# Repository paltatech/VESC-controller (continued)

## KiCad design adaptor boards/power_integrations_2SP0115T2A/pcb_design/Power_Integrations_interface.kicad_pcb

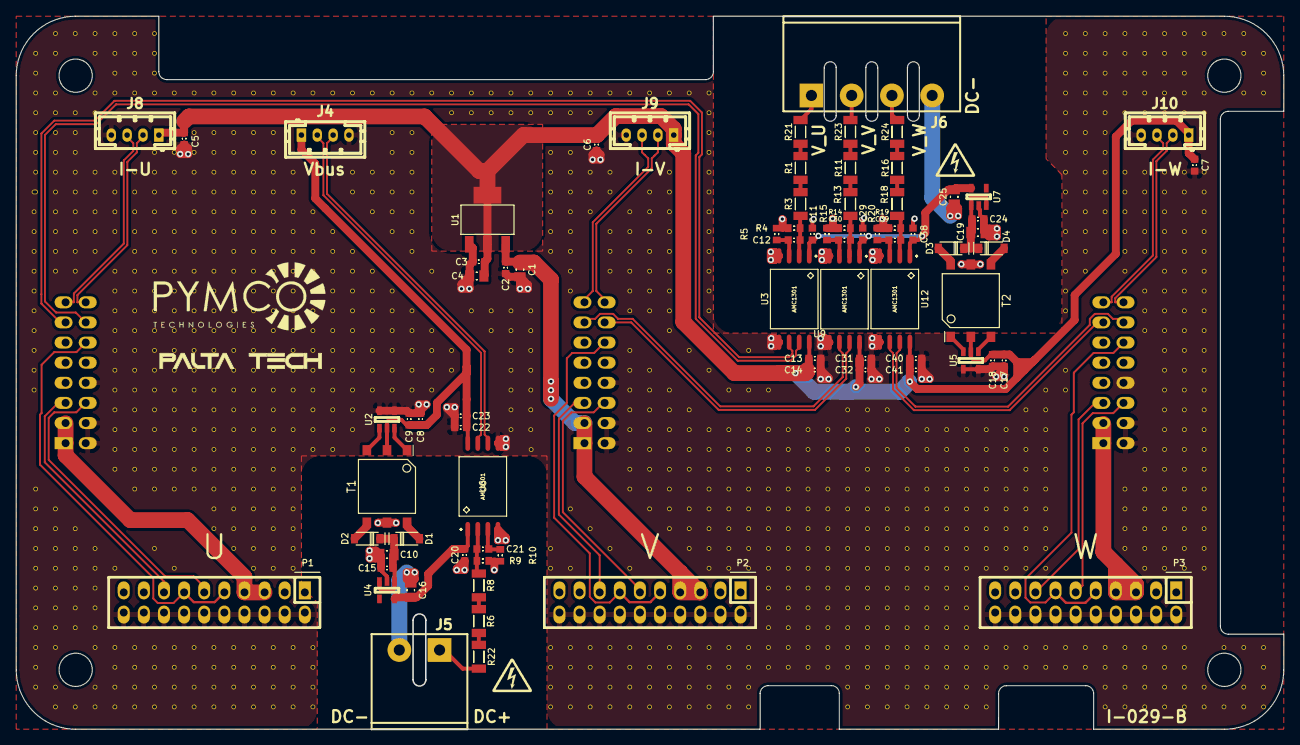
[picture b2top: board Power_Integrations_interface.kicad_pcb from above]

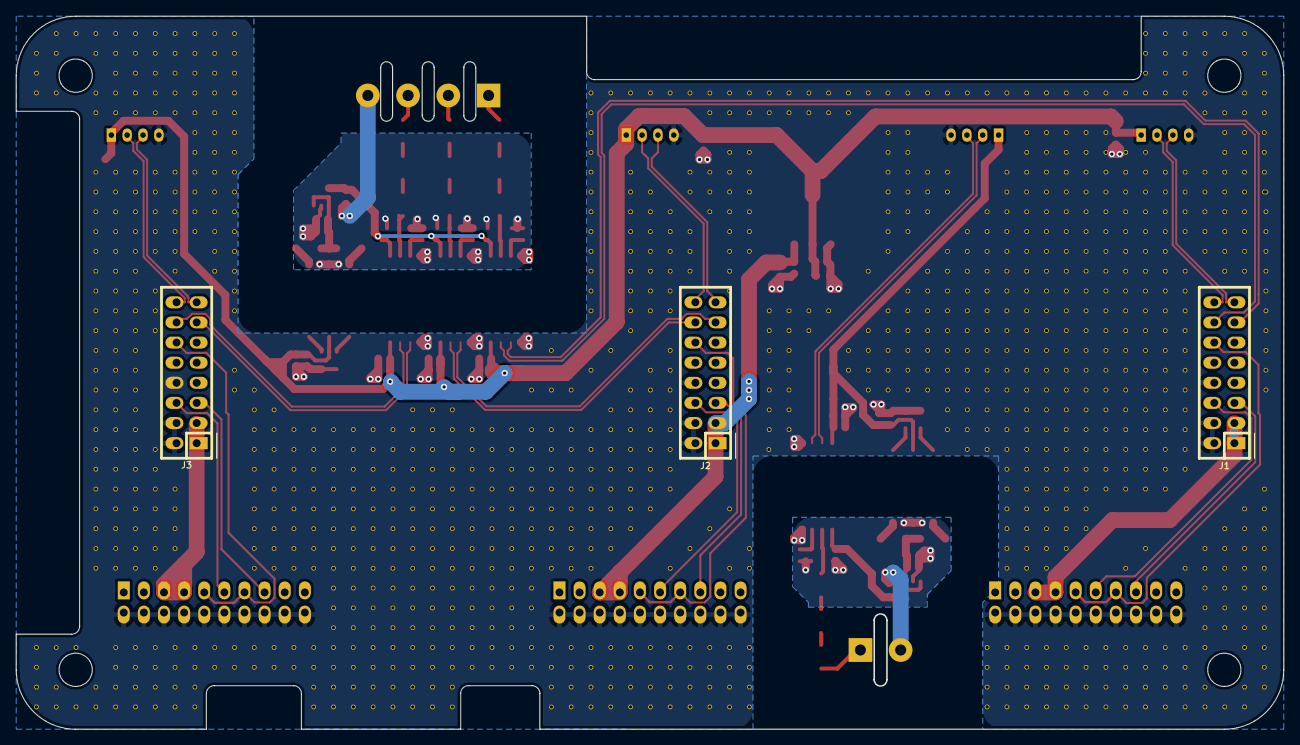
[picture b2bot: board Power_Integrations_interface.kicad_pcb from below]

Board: 2 copper layers, 160.0 x 90.0 mm, 1122 parts (3 on the bottom side), 63 nets.

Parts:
C1, C4, C10, C16, C19, C25: 22uF; CAPC2012X70
C2, C3, C5, C6, C7, C9, C11, C13, C15, C18, C20, C22, C24, C29, C31, C38, C40: 100nF; CAPC1608X55
C8, C14, C17, C23, C32, C41: 2.2uF; CAPC1608X55
C12, C21, C30, C39: 330pF; CAPC1608X55
D1, D2, D3, D4: MBR0520; SOD-123
J1: GATE_DRIVER_CONN_U; CONN-100MIL-M-2x8
J2: GATE_DRIVER_CONN_V; CONN-100MIL-M-2x8
J3: GATE_DRIVER_CONN_W; CONN-100MIL-M-2x8
J4: VBUS; b4b-ph-kl
J5: CONN-100MIL-F-1x2; mstba_2,5%2f2-g-5,08
J6: Phoenix 1757268 5.08mm; mstba_2,5%2f4-g-5,08
J8, J9, J10: current sensor; b4b-ph-kl
P1, P2, P3: 2SP0115T_conector; CONN-100MIL-F-2x10
R1, R3, R6, R8, R11, R13, R16, R18, R21, R22, R23, R24: 500k; RESC3216X60
R4, R5, R9, R10, R14, R15, R19, R20: 1k; RESC1608X50
T1, T2: TRANS-2CT; WURTH-760390014
U1: LM1117IMP-v.v; SOT-223
U2, U5: SN6501DBV; SOT-23-5
U3, U6, U9, U12: AMC1301; SOIC127P1032X265-8
U4, U7: TPS76350; SOT-23-5
V1_2, V1_3, V1_3#2, V1_4, V1_4#2, V1_5, V1_5#2, V1_6, V1_6#2, V1_7, V1_7#2, V1_7#3, V1_8, V1_8#2, V1_8#3, V1_8#4, V1_9, V1_9#2, V1_9#3, V1_24, V1_25, V1_26, V1_27, V1_28, V1_29, V1_30, V1_31, V1_32, V1_33, V1_34, V2_1, V2_2, V2_4, V2_5, V2_6, V2_7, V2_8, V2_11, V2_11#2, V2_12, V2_12#2, V2_25, V2_26, V2_27, V2_28, V2_29, V2_30, V2_31, V2_32, V2_34, V2_35, V3_1, V3_5, V3_6, V3_7, V3_10, V3_10#2, V3_11, V3_12, V3_12#2, V3_26, V3_27, V3_28, V3_29, V3_29#2, V3_30, V3_30#2, V3_31, V3_31#2, V3_35, V4_1, V4_2, V4_4, V4_5, V4_9, V4_9#2, V4_10, V4_10#2, V4_10#3, V4_11, V4_12, V4_27, V4_28, V4_34, V4_34#2, V4_35, V5_1, V5_2, V5_3, V5_4, V5_8, V5_9, V5_10, V5_11, V5_28, V5_34, V5_34#2, V5_34#3, V5_35, V6_1, V6_2, V6_3, V6_4, V6_8, V6_9, V6_10, V6_12, V6_12#2, V6_13, V6_13#2, V6_14, V6_14#2, V6_15, V6_15#2, V6_16, V6_16#2, V6_17, V6_17#2, V6_17#3, V6_17#4, V6_17#5, V6_17#6, V6_18, V6_18#2, V6_19, V6_19#2, V6_20, V6_20#2, V6_21, V6_21#2, V6_22, V6_22#2, V6_23, V6_23#2, V6_24, V6_34, V6_34#2, V6_34#3, V6_35, V7_1, V7_2, V7_3, V7_7, V7_8, V7_9, V7_11, V7_11#2, V7_12, V7_13, V7_14, V7_15, V7_16, V7_17, V7_17#2, V7_17#3, V7_18, V7_19, V7_20, V7_21, V7_22, V7_23, V7_24, V7_27, V7_34, V7_34#2, V7_34#3, V7_35, V8_8, V8_10, V8_10#2, V8_10#3, V8_11, V8_12, V8_13, V8_14, V8_15, V8_16, V8_17, V8_17#2, V8_17#3, V8_18, V8_19, V8_20, V8_21, V8_22, V8_23, V8_24, V8_28, V8_34, V8_34#2, V8_34#3, V8_35, V9_9, V9_9#2, V9_9#3, V9_9#4, V9_10, V9_11, V9_12, V9_13, V9_14, V9_15, V9_16, V9_17, V9_17#2, V9_17#3, V9_18, V9_19, V9_20, V9_21, V9_22, V9_23, V9_24, V9_34, V9_34#2, V9_34#3, V9_35, V10_8, V10_8#2, V10_9, V10_9#2, V10_10, V10_11, V10_12, V10_13, V10_14, V10_15, V10_16, V10_17, V10_17#2, V10_17#3, V10_18, V10_19, V10_20, V10_21, V10_22, V10_23, V10_24, V10_25, V10_26, V10_34, V10_34#2, V10_34#3, V10_35, V11_8, V11_8#2, V11_9, V11_9#2, V11_10, V11_11, V11_12, V11_13, V11_14, V11_15, V11_16, V11_17, V11_17#2, V11_17#3, V11_18, V11_19, V11_20, V11_21, V11_22, V11_23, V11_24, V11_25, V11_26, V11_27, V11_34, V11_34#2, V11_34#3, V11_35, V12_8, V12_8#2, V12_9, V12_9#2, V12_10, V12_11, V12_12, V12_13, V12_14, V12_15, V12_16, V12_17, V12_17#2, V12_17#3, V12_18, V12_19, V12_20, V12_21, V12_22, V12_23, V12_24, V12_25, V12_26, V12_27, V12_28, V12_34, V12_34#2, V12_34#3, V12_35, V13_8, V13_8#2, V13_9, V13_9#2, V13_10, V13_11, V13_12, V13_13, V13_14, V13_15, V13_16, V13_17, V13_17#2, V13_17#3, V13_18, V13_19, V13_20, V13_21, V13_22, V13_23, V13_24, V13_25, V13_26, V13_27, V13_28, V13_34, V13_34#2, V13_34#3, V13_35, V14_8, V14_9, V14_10, V14_11, V14_12, V14_13, V14_14, V14_15, V14_16, V14_17, V14_17#2, V14_17#3, V14_18, V14_19, V14_20, V14_21, V14_22, V14_23, V14_24, V14_25, V14_26, V14_27, V14_28, V14_34, V14_34#2, V14_34#3, V14_35, V15_10, V15_11, V15_12, V15_13, V15_14, V15_15, V15_16, V15_17, V15_17#2, V15_18, V15_19, V15_20, V15_21, V15_22, V15_34, V15_34#2, V15_34#3, V15_35, V16_11, V16_12, V16_13, V16_14, V16_15, V16_16, V16_17, V16_17#2, V16_18, V16_19, V16_19#2, V16_20, V16_20#2, V16_21, V16_21#2, V16_22, V17_8, V17_9, V17_12, V17_13, V17_14, V17_15, V17_16, V17_17, V17_17#2, V17_18, V18_8, V18_9, V18_10, V18_13, V18_14, V18_15, V18_16, V18_17, V18_17#2, V18_18, V18_18#2, V19_6, V19_7, V19_8, V19_9, V19_10, V19_11, V19_14, V19_15, V19_16, V19_17, V19_17#2, V19_18, V19_18#2, V20_6, V20_7, V20_8, V20_9, V20_10, V20_11, V20_12, V20_15, V20_16, V20_17, V20_17#2, V20_18, V20_18#2, V21_13, V21_16, V21_17, V21_17#2, V21_18, V21_18#2, V22_5, V22_17, V22_17#2, V22_18, V23_5, V23_15, V24_5, V24_15, V24_16, V25_5, V25_15, V25_16, V25_17, V25_18, V25_19, V25_20, V25_20#2, V26_5, V26_5#2, V26_15, V26_16, V26_17, V26_18, V26_19, V26_20, V26_20#2, V26_20#3, V27_5, V27_5#2, V27_7, V27_7#2, V27_8, V27_9, V27_9#2, V27_10, V27_10#2, V27_27, V27_28, V27_34, V27_34#2, V27_34#3, V27_34#4, V27_35, V28_9, V28_9#2, V28_10, V28_10#2, V28_11, V28_11#2, V28_12, V28_12#2, V28_25, V28_28, V28_34, V28_34#2, V28_34#3, V28_34#4, V28_35, V29_9, V29_9#2, V29_9#3, V29_9#4, V29_26, V29_34, V29_34#2, V29_34#3, V29_34#4, V29_35, V30_11, V30_12, V30_12#2, V30_27, V30_34, V30_34#2, V30_34#3, V30_34#4, V30_35, V31_10, V31_11, V31_12, V31_12#2, V31_12#3, V31_12#4, V31_24, V31_28, V31_34, V31_34#2, V31_34#3, V31_34#4, V31_35, V32_9, V32_10, V32_11, V32_12, V32_13, V32_14, V32_15, V32_18, V32_18#2, V32_19, V32_19#2, V32_19#3, V32_20, V32_20#2, V32_21, V32_21#2, V32_22, V32_22#2, V32_23, V32_23#2, V32_24, V32_25, V32_34, V32_34#2, V32_34#3, V32_34#4, V32_34#5, V32_35, V33_8, V33_8#2, V33_8#3, V33_9, V33_9#2, V33_9#3, V33_10, V33_10#2, V33_11, V33_11#2, V33_12, V33_12#2, V33_13, V33_13#2, V33_14, V33_14#2, V33_15, V33_15#2, V33_16, V33_16#2, V33_19, V33_20, V33_21, V33_22, V33_23, V33_24, V33_25, V33_26, V33_34, V33_34#2, V33_34#3, V33_34#4, V33_34#5, V33_35, V34_17, V34_20, V34_21, V34_22, V34_23, V34_24, V34_25, V34_26, V34_27, V34_34, V34_34#2, V34_34#3, V34_34#4, V34_34#5, V34_35, V35_4, V35_18, V35_21, V35_22, V35_23, V35_24, V35_25, V35_26, V35_27, V35_28, V35_34, V35_34#2, V35_34#3, V35_34#4, V35_34#5, V35_35, V36_19, V36_19#2, V36_21, V36_22, V36_23, V36_24, V36_25, V36_26, V36_27, V36_28, V36_34, V36_34#2, V36_34#3, V36_34#4, V36_34#5, V36_35, V37_19, V37_21, V37_22, V37_23, V37_24, V37_25, V37_26, V37_27, V37_28, V37_34, V37_34#2, V37_34#3, V37_34#4, V37_34#5, V37_35, V38_19, V38_21, V38_22, V38_23, V38_24, V38_25, V38_26, V38_27, V38_28, V38_34, V38_34#2, V38_34#3, V39_21, V39_22, V39_23, V39_24, V39_25, V39_26, V39_27, V39_28, V39_29, V39_29#2, V39_30, V39_30#2, V39_31, V39_31#2, V39_32, V39_32#2, V39_33, V40_21, V40_22, V40_23, V40_24, V40_25, V40_26, V40_27, V40_28, V40_29, V40_30, V40_31, V40_32, V40_33, V41_21, V41_22, V41_23, V41_24, V41_25, V41_26, V41_27, V41_28, V41_29, V41_30, V41_31, V41_32, V41_33, V42_20, V42_21, V42_22, V42_23, V42_24, V42_25, V42_26, V42_27, V42_28, V42_29, V42_30, V42_31, V42_32, V42_33, V42_34, V42_35, V43_20, V43_21, V43_22, V43_23, V43_24, V43_25, V43_26, V43_27, V43_28, V43_29, V43_30, V43_31, V43_32, V43_33, V43_34, V43_35, V44_20, V44_21, V44_22, V44_23, V44_24, V44_25, V44_26, V44_27, V44_28, V44_29, V44_30, V44_31, V44_32, V44_33, V44_34, V44_35, V45_21, V45_22, V45_23, V45_24, V45_25, V45_26, V45_27, V45_28, V45_29, V45_30, V45_31, V45_32, V45_33, V45_34, V45_35, V46_21, V46_22, V46_23, V46_24, V46_25, V46_26, V46_27, V46_28, V46_29, V46_30, V46_31, V46_32, V46_33, V46_34, V46_35, V47_21, V47_22, V47_23, V47_24, V47_25, V47_26, V47_27, V47_28, V47_29, V47_30, V47_30#2, V47_31, V47_31#2, V47_32, V47_32#2, V47_33, V47_34, V47_35, V48_21, V48_22, V48_23, V48_24, V48_25, V48_26, V48_27, V48_28, V48_28#2, V48_34, V48_35, V49_21, V49_22, V49_23, V49_24, V49_25, V49_26, V49_27, V49_28, V49_28#2, V49_34, V49_35, V50_21, V50_22, V50_23, V50_24, V50_25, V50_26, V50_27, V50_28, V50_28#2, V51_20, V51_21, V51_22, V51_23, V51_24, V51_25, V51_26, V51_27, V51_28, V51_28#2, V52_19, V52_20, V52_21, V52_22, V52_23, V52_24, V52_25, V52_26, V52_27, V52_28, V52_28#2, V53_1, V53_2, V53_3, V53_4, V53_4#2, V53_10, V53_11, V53_12, V53_13, V53_14, V53_15, V53_18, V53_19, V54_1, V54_2, V54_3, V54_4, V54_4#2, V54_12, V54_12#2, V55_1, V55_2, V55_3, V55_4, V55_4#2, V55_10, V55_11, V55_34, V55_35, V56_1, V56_2, V56_3, V56_4, V56_8, V56_9, V56_10, V56_11, V56_12, V56_12#2, V56_24, V56_25, V56_26, V56_27, V56_34, V56_35, V57_1, V57_2, V57_3, V57_4, V57_5, V57_6, V57_6#2, V57_7, V57_7#2, V57_8, V57_9, V57_10, V57_11, V57_12, V57_24, V57_24#2, V57_25, V57_25#2, V57_26, V57_27, V57_28, V57_34, V57_35, V58_1, V58_2, V58_3, V58_4, V58_5, V58_6, V58_6#2, V58_6#3, V58_7, V58_7#2, V58_7#3, V58_8, V58_9, V58_10, V58_11, V58_12, V58_13, V58_14, V58_14#2, V58_15, V58_15#2, V58_16, V58_16#2, V58_17, V58_18, V58_19, V58_20, V58_21, V58_22, V58_23, V58_24, V58_25, V58_26, V58_27, V58_28, V58_34, V58_35, V59_1, V59_2, V59_3, V59_4, V59_5, V59_6, V59_6#2, V59_7, V59_7#2, V59_8, V59_9, V59_10, V59_11, V59_12, V59_13, V59_14, V59_15, V59_16, V59_17, V59_18, V59_19, V59_20, V59_21, V59_22, V59_23, V59_24, V59_25, V59_26, V59_27, V59_28, V59_34, V59_35, V60_1, V60_2, V60_4, V60_5, V60_6, V60_8, V60_9, V60_10, V60_11, V60_12, V60_13, V60_14, V60_15, V60_16, V60_17, V60_18, V60_19, V60_20, V60_21, V60_22, V60_23, V60_24, V60_25, V60_26, V60_27, V60_28, V60_34, V60_35, V61_1, V61_32, V61_35, V62_1, V62_2, V62_4, V62_32, V62_34, V62_35, V63_2, V63_3, V63_4, V63_32, V63_33, V63_34, V63_35: AUTO_VIA; VIA_MATRIX

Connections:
15v_U: J1.1, J1.3, P1.5, P1.7
15v_V: C1.1, C2.1, J2.1, J2.3, P2.5, P2.7, U1.3
15v_W: J3.1, J3.3, P3.5, P3.7
+5: C3.1, C4.1, C5.1, C6.1, C7.1, C13.1, C14.1, C17.1, C18.1, C31.1, C32.1, C40.1, C41.1, J8.1, J9.1, J10.1, T2.2, U1.2, U1.4, U3.8, U5.2, U9.8, U12.8
+5A: C11.2, C25.1, C29.2, C38.2, U3.1, U7.5, U9.1, U12.1
/I_phase_U+: J1.16, J8.2
/I_phase_U-: J1.15, J8.3
/I_phase_V+: J2.16, J9.2
/I_phase_V-: J2.15, J9.3
/I_phase_W+: J3.16, J10.2
/I_phase_W-: J3.15, J10.3
/V_BUS/GND2: C10.2, C15.2, C16.2, C20.1, J5.2, R9.2, R10.1, T1.5, U4.2, U6.4
/V_BUS/VDD1: C8.1, C9.1, C22.1, C23.1, J4.1, T1.2, U2.2, U6.8
/V_BUS/VDD2: C16.1, C20.2, U4.5, U6.1
/V_BUS/VIN+: C21.1, R8.1, R9.1, U6.2
/V_BUS/VIN-: C21.2, R10.2, U6.3
/V_BUS/Vin+: J5.1, R22.2
/V_phase_U/VIN+: C12.1, R3.1, R4.1, U3.2
/V_phase_U/VIN-: C12.2, R5.2, U3.3
/V_phase_U/Vin+: J6.1, R21.2
/V_phase_U/Vout+: J1.14, U3.7
/V_phase_U/Vout-: J1.13, U3.6
/V_phase_V/VIN+: C30.1, R13.1, R14.1, U9.2
/V_phase_V/VIN-: C30.2, R15.2, U9.3
/V_phase_V/Vin+: J6.2, R23.2
/V_phase_V/Vout+: J2.14, U9.7
/V_phase_V/Vout-: J2.13, U9.6
/V_phase_W/VIN+: C39.1, R18.1, R19.1, U12.2
/V_phase_W/VIN-: C39.2, R20.2, U12.3
/V_phase_W/Vin+: J6.3, R24.2
/V_phase_W/Vout+: J3.14, U12.7
/V_phase_W/Vout-: J3.13, U12.6
/vbus+: J4.2, U6.7
/vbus-: J4.3, U6.6
GND: C1.2, C2.2, C3.2, C4.2, C5.2, C6.2, C7.2, C8.2, C9.2, C13.2, C14.2, C17.2, C18.2, C22.2, C23.2, C31.2, C32.2, C40.2, C41.2, J1.2, J1.4, J1.8, J2.2, J2.4, J2.8, J3.2, J3.4, J3.8, J4.4, J8.4, J9.4, J10.4, P1.2, P1.4, P1.6, P1.8, P1.10, P1.12, P1.14, P1.16, P1.18, P1.20, P2.2, P2.4, P2.6, P2.8, P2.10, P2.12, P2.14, P2.16, P2.18, P2.20, P3.2, P3.4, P3.6, P3.8, P3.10, P3.12, P3.14, P3.16, P3.18, P3.20, U1.1, U2.4, U2.5, U3.5, U5.4, U5.5, U6.5, U9.5, U12.5, V1_2.1, V1_3.1, V1_3#2.1, V1_4.1, V1_4#2.1, V1_5.1, V1_5#2.1, V1_6.1, V1_6#2.1, V1_7.1, V1_7#2.1, V1_7#3.1, V1_8.1, V1_8#2.1, V1_8#3.1, V1_8#4.1, V1_9.1, V1_9#2.1, V1_9#3.1, V1_24.1, V1_25.1, V1_26.1, V1_27.1, V1_28.1, V1_29.1, V1_30.1, V1_31.1, V1_32.1, V1_33.1, V1_34.1, V2_1.1, V2_2.1, V2_4.1, V2_5.1, V2_6.1, V2_7.1, V2_8.1, V2_11.1, V2_11#2.1, V2_12.1, V2_12#2.1, V2_25.1, V2_26.1, V2_27.1, V2_28.1, V2_29.1, V2_30.1, V2_31.1, V2_32.1, V2_34.1, V2_35.1, V3_1.1, V3_5.1, V3_6.1, V3_7.1, V3_10.1, V3_10#2.1, V3_11.1, V3_12.1, V3_12#2.1, V3_26.1, V3_27.1, V3_28.1, V3_29.1, V3_29#2.1, V3_30.1, V3_30#2.1, V3_31.1, V3_31#2.1, V3_35.1, V4_1.1, V4_2.1, V4_4.1, V4_5.1, V4_9.1, V4_9#2.1, V4_10.1, V4_10#2.1, V4_10#3.1, V4_11.1, V4_12.1, V4_27.1, V4_28.1, V4_34.1, V4_34#2.1, V4_35.1, V5_1.1, V5_2.1, V5_3.1, V5_4.1, V5_8.1, V5_9.1, V5_10.1, V5_11.1, V5_28.1, V5_34.1, V5_34#2.1, V5_34#3.1, V5_35.1, V6_1.1, V6_2.1, V6_3.1, V6_4.1, V6_8.1, V6_9.1, V6_10.1, V6_12.1, V6_12#2.1, V6_13.1, V6_13#2.1, V6_14.1, V6_14#2.1, V6_15.1, V6_15#2.1, V6_16.1, V6_16#2.1, V6_17.1, V6_17#2.1, V6_17#3.1, V6_17#4.1, V6_17#5.1, V6_17#6.1, V6_18.1, V6_18#2.1, V6_19.1, V6_19#2.1, V6_20.1, V6_20#2.1, V6_21.1, V6_21#2.1, V6_22.1, V6_22#2.1, V6_23.1, V6_23#2.1, V6_24.1, V6_34.1, V6_34#2.1, V6_34#3.1, V6_35.1, V7_1.1, V7_2.1, V7_3.1, V7_7.1, V7_8.1, V7_9.1, V7_11.1, V7_11#2.1, V7_12.1, V7_13.1, V7_14.1, V7_15.1, V7_16.1, V7_17.1, V7_17#2.1, V7_17#3.1, V7_18.1, V7_19.1, V7_20.1, V7_21.1, V7_22.1, V7_23.1, V7_24.1, V7_27.1, V7_34.1, V7_34#2.1, V7_34#3.1, V7_35.1, V8_8.1, V8_10.1, V8_10#2.1, V8_10#3.1, V8_11.1, V8_12.1, V8_13.1, V8_14.1, V8_15.1, V8_16.1, V8_17.1, V8_17#2.1, V8_17#3.1, V8_18.1, V8_19.1, V8_20.1, V8_21.1, V8_22.1, V8_23.1, V8_24.1, V8_28.1, V8_34.1, V8_34#2.1, V8_34#3.1, V8_35.1, V9_9.1, V9_9#2.1, V9_9#3.1, V9_9#4.1, V9_10.1, V9_11.1, V9_12.1, V9_13.1, V9_14.1, V9_15.1, V9_16.1, V9_17.1, V9_17#2.1, V9_17#3.1, V9_18.1, V9_19.1, V9_20.1, V9_21.1, V9_22.1, V9_23.1, V9_24.1, V9_34.1, V9_34#2.1, V9_34#3.1, V9_35.1, V10_8.1, V10_8#2.1, V10_9.1, V10_9#2.1, V10_10.1, V10_11.1, V10_12.1, V10_13.1, V10_14.1, V10_15.1, V10_16.1, V10_17.1, V10_17#2.1, V10_17#3.1, V10_18.1, V10_19.1, V10_20.1, V10_21.1, V10_22.1, V10_23.1, V10_24.1, V10_25.1, V10_26.1, V10_34.1, V10_34#2.1, V10_34#3.1, V10_35.1, V11_8.1, V11_8#2.1, V11_9.1, V11_9#2.1, V11_10.1, V11_11.1, V11_12.1, V11_13.1, V11_14.1, V11_15.1, V11_16.1, V11_17.1, V11_17#2.1, V11_17#3.1, V11_18.1, V11_19.1, V11_20.1, V11_21.1, V11_22.1, V11_23.1, V11_24.1, V11_25.1, V11_26.1, V11_27.1, V11_34.1, V11_34#2.1, V11_34#3.1, V11_35.1, V12_8.1, V12_8#2.1, V12_9.1, V12_9#2.1, V12_10.1, V12_11.1, V12_12.1, V12_13.1, V12_14.1, V12_15.1, V12_16.1, V12_17.1, V12_17#2.1, V12_17#3.1, V12_18.1, V12_19.1, V12_20.1, V12_21.1, V12_22.1, V12_23.1, V12_24.1, V12_25.1, V12_26.1, V12_27.1, V12_28.1, V12_34.1, V12_34#2.1, V12_34#3.1, V12_35.1, V13_8.1, V13_8#2.1, V13_9.1, V13_9#2.1, V13_10.1, V13_11.1, V13_12.1, V13_13.1, V13_14.1, V13_15.1, V13_16.1, V13_17.1, V13_17#2.1, V13_17#3.1, V13_18.1, V13_19.1, V13_20.1, V13_21.1, V13_22.1, V13_23.1, V13_24.1, V13_25.1, V13_26.1, V13_27.1, V13_28.1, V13_34.1, V13_34#2.1, V13_34#3.1, V13_35.1, V14_8.1, V14_9.1, V14_10.1, V14_11.1, V14_12.1, V14_13.1, V14_14.1, V14_15.1, V14_16.1, V14_17.1, V14_17#2.1, V14_17#3.1, V14_18.1, V14_19.1, V14_20.1, V14_21.1, V14_22.1, V14_23.1, V14_24.1, V14_25.1, V14_26.1, V14_27.1, V14_28.1, V14_34.1, V14_34#2.1, V14_34#3.1, V14_35.1, V15_10.1, V15_11.1, V15_12.1, V15_13.1, V15_14.1, V15_15.1, V15_16.1, V15_17.1, V15_17#2.1, V15_18.1, V15_19.1, V15_20.1, V15_21.1, V15_22.1, V15_34.1, V15_34#2.1, V15_34#3.1, V15_35.1, V16_11.1, V16_12.1, V16_13.1, V16_14.1, V16_15.1, V16_16.1, V16_17.1, V16_17#2.1, V16_18.1, V16_19.1, V16_19#2.1, V16_20.1, V16_20#2.1, V16_21.1, V16_21#2.1, V16_22.1, V17_8.1, V17_9.1, V17_12.1, V17_13.1, V17_14.1, V17_15.1, V17_16.1, V17_17.1, V17_17#2.1, V17_18.1, V18_8.1, V18_9.1, V18_10.1, V18_13.1, V18_14.1, V18_15.1, V18_16.1, V18_17.1, V18_17#2.1, V18_18.1, V18_18#2.1, V19_6.1, V19_7.1, V19_8.1, V19_9.1, V19_10.1, V19_11.1, V19_14.1, V19_15.1, V19_16.1, V19_17.1, V19_17#2.1, V19_18.1, V19_18#2.1, V20_6.1, V20_7.1, V20_8.1, V20_9.1, V20_10.1, V20_11.1, V20_12.1, V20_15.1, V20_16.1, V20_17.1, V20_17#2.1, V20_18.1, V20_18#2.1, V21_13.1, V21_16.1, V21_17.1, V21_17#2.1, V21_18.1, V21_18#2.1, V22_5.1, V22_17.1, V22_17#2.1, V22_18.1, V23_5.1, V23_15.1, V24_5.1, V24_15.1, V24_16.1, V25_5.1, V25_15.1, V25_16.1, V25_17.1, V25_18.1, V25_19.1, V25_20.1, V25_20#2.1, V26_5.1, V26_5#2.1, V26_15.1, V26_16.1, V26_17.1, V26_18.1, V26_19.1, V26_20.1, V26_20#2.1, V26_20#3.1, V27_5.1, V27_5#2.1, V27_7.1, V27_7#2.1, V27_8.1, V27_9.1, V27_9#2.1, V27_10.1, V27_10#2.1, V27_27.1, V27_28.1, V27_34.1, V27_34#2.1, V27_34#3.1, V27_34#4.1, V27_35.1, V28_9.1, V28_9#2.1, V28_10.1, V28_10#2.1, V28_11.1, V28_11#2.1, V28_12.1, V28_12#2.1, V28_25.1, V28_28.1, V28_34.1, V28_34#2.1, V28_34#3.1, V28_34#4.1, V28_35.1, V29_9.1, V29_9#2.1, V29_9#3.1, V29_9#4.1, V29_26.1, V29_34.1, V29_34#2.1, V29_34#3.1, V29_34#4.1, V29_35.1, V30_11.1, V30_12.1, V30_12#2.1, V30_27.1, V30_34.1, V30_34#2.1, V30_34#3.1, V30_34#4.1, V30_35.1, V31_10.1, V31_11.1, V31_12.1, V31_12#2.1, V31_12#3.1, V31_12#4.1, V31_24.1, V31_28.1, V31_34.1, V31_34#2.1, V31_34#3.1, V31_34#4.1, V31_35.1, V32_9.1, V32_10.1, V32_11.1, V32_12.1, V32_13.1, V32_14.1, V32_15.1, V32_18.1, V32_18#2.1, V32_19.1, V32_19#2.1, V32_19#3.1, V32_20.1, V32_20#2.1, V32_21.1, V32_21#2.1, V32_22.1, V32_22#2.1, V32_23.1, V32_23#2.1, V32_24.1, V32_25.1, V32_34.1, V32_34#2.1, V32_34#3.1, V32_34#4.1, V32_34#5.1, V32_35.1, V33_8.1, V33_8#2.1, V33_8#3.1, V33_9.1, V33_9#2.1, V33_9#3.1, V33_10.1, V33_10#2.1, V33_11.1, V33_11#2.1, V33_12.1, V33_12#2.1, V33_13.1, V33_13#2.1, V33_14.1, V33_14#2.1, V33_15.1, V33_15#2.1, V33_16.1, V33_16#2.1, V33_19.1, V33_20.1, V33_21.1, V33_22.1, V33_23.1, V33_24.1, V33_25.1, V33_26.1, V33_34.1, V33_34#2.1, V33_34#3.1, V33_34#4.1, V33_34#5.1, V33_35.1, V34_17.1, V34_20.1, V34_21.1, V34_22.1, V34_23.1, V34_24.1, V34_25.1, V34_26.1, V34_27.1, V34_34.1, V34_34#2.1, V34_34#3.1, V34_34#4.1, V34_34#5.1, V34_35.1, V35_4.1, V35_18.1, V35_21.1, V35_22.1, V35_23.1, V35_24.1, V35_25.1, V35_26.1, V35_27.1, V35_28.1, V35_34.1, V35_34#2.1, V35_34#3.1, V35_34#4.1, V35_34#5.1, V35_35.1, V36_19.1, V36_19#2.1, V36_21.1, V36_22.1, V36_23.1, V36_24.1, V36_25.1, V36_26.1, V36_27.1, V36_28.1, V36_34.1, V36_34#2.1, V36_34#3.1, V36_34#4.1, V36_34#5.1, V36_35.1, V37_19.1, V37_21.1, V37_22.1, V37_23.1, V37_24.1, V37_25.1, V37_26.1, V37_27.1, V37_28.1, V37_34.1, V37_34#2.1, V37_34#3.1, V37_34#4.1, V37_34#5.1, V37_35.1, V38_19.1, V38_21.1, V38_22.1, V38_23.1, V38_24.1, V38_25.1, V38_26.1, V38_27.1, V38_28.1, V38_34.1, V38_34#2.1, V38_34#3.1, V39_21.1, V39_22.1, V39_23.1, V39_24.1, V39_25.1, V39_26.1, V39_27.1, V39_28.1, V39_29.1, V39_29#2.1, V39_30.1, V39_30#2.1, V39_31.1, V39_31#2.1, V39_32.1, V39_32#2.1, V39_33.1, V40_21.1, V40_22.1, V40_23.1, V40_24.1, V40_25.1, V40_26.1, V40_27.1, V40_28.1, V40_29.1, V40_30.1, V40_31.1, V40_32.1, V40_33.1, V41_21.1, V41_22.1, V41_23.1, V41_24.1, V41_25.1, V41_26.1, V41_27.1, V41_28.1, V41_29.1, V41_30.1, V41_31.1, V41_32.1, V41_33.1, V42_20.1, V42_21.1, V42_22.1, V42_23.1, V42_24.1, V42_25.1, V42_26.1, V42_27.1, V42_28.1, V42_29.1, V42_30.1, V42_31.1, V42_32.1, V42_33.1, V42_34.1, V42_35.1, V43_20.1, V43_21.1, V43_22.1, V43_23.1, V43_24.1, V43_25.1, V43_26.1, V43_27.1, V43_28.1, V43_29.1, V43_30.1, V43_31.1, V43_32.1, V43_33.1, V43_34.1, V43_35.1, V44_20.1, V44_21.1, V44_22.1, V44_23.1, V44_24.1, V44_25.1, V44_26.1, V44_27.1, V44_28.1, V44_29.1, V44_30.1, V44_31.1, V44_32.1, V44_33.1, V44_34.1, V44_35.1, V45_21.1, V45_22.1, V45_23.1, V45_24.1, V45_25.1, V45_26.1, V45_27.1, V45_28.1, V45_29.1, V45_30.1, V45_31.1, V45_32.1, V45_33.1, V45_34.1, V45_35.1, V46_21.1, V46_22.1, V46_23.1, V46_24.1, V46_25.1, V46_26.1, V46_27.1, V46_28.1, V46_29.1, V46_30.1, V46_31.1, V46_32.1, V46_33.1, V46_34.1, V46_35.1, V47_21.1, V47_22.1, V47_23.1, V47_24.1, V47_25.1, V47_26.1, V47_27.1, V47_28.1, V47_29.1, V47_30.1, V47_30#2.1, V47_31.1, V47_31#2.1, V47_32.1, V47_32#2.1, V47_33.1, V47_34.1, V47_35.1, V48_21.1, V48_22.1, V48_23.1, V48_24.1, V48_25.1, V48_26.1, V48_27.1, V48_28.1, V48_28#2.1, V48_34.1, V48_35.1, V49_21.1, V49_22.1, V49_23.1, V49_24.1, V49_25.1, V49_26.1, V49_27.1, V49_28.1, V49_28#2.1, V49_34.1, V49_35.1, V50_21.1, V50_22.1, V50_23.1, V50_24.1, V50_25.1, V50_26.1, V50_27.1, V50_28.1, V50_28#2.1, V51_20.1, V51_21.1, V51_22.1, V51_23.1, V51_24.1, V51_25.1, V51_26.1, V51_27.1, V51_28.1, V51_28#2.1, V52_19.1, V52_20.1, V52_21.1, V52_22.1, V52_23.1, V52_24.1, V52_25.1, V52_26.1, V52_27.1, V52_28.1, V52_28#2.1, V53_1.1, V53_2.1, V53_3.1, V53_4.1, V53_4#2.1, V53_10.1, V53_11.1, V53_12.1, V53_13.1, V53_14.1, V53_15.1, V53_18.1, V53_19.1, V54_1.1, V54_2.1, V54_3.1, V54_4.1, V54_4#2.1, V54_12.1, V54_12#2.1, V55_1.1, V55_2.1, V55_3.1, V55_4.1, V55_4#2.1, V55_10.1, V55_11.1, V55_34.1, V55_35.1, V56_1.1, V56_2.1, V56_3.1, V56_4.1, V56_8.1, V56_9.1, V56_10.1, V56_11.1, V56_12.1, V56_12#2.1, V56_24.1, V56_25.1, V56_26.1, V56_27.1, V56_34.1, V56_35.1, V57_1.1, V57_2.1, V57_3.1, V57_4.1, V57_5.1, V57_6.1, V57_6#2.1, V57_7.1, V57_7#2.1, V57_8.1, V57_9.1, V57_10.1, V57_11.1, V57_12.1, V57_24.1, V57_24#2.1, V57_25.1, V57_25#2.1, V57_26.1, V57_27.1, V57_28.1, V57_34.1, V57_35.1, V58_1.1, V58_2.1, V58_3.1, V58_4.1, V58_5.1, V58_6.1, V58_6#2.1, V58_6#3.1, V58_7.1, V58_7#2.1, V58_7#3.1, V58_8.1, V58_9.1, V58_10.1, V58_11.1, V58_12.1, V58_13.1, V58_14.1, V58_14#2.1, V58_15.1, V58_15#2.1, V58_16.1, V58_16#2.1, V58_17.1, V58_18.1, V58_19.1, V58_20.1, V58_21.1, V58_22.1, V58_23.1, V58_24.1, V58_25.1, V58_26.1, V58_27.1, V58_28.1, V58_34.1, V58_35.1, V59_1.1, V59_2.1, V59_3.1, V59_4.1, V59_5.1, V59_6.1, V59_6#2.1, V59_7.1, V59_7#2.1, V59_8.1, V59_9.1, V59_10.1, V59_11.1, V59_12.1, V59_13.1, V59_14.1, V59_15.1, V59_16.1, V59_17.1, V59_18.1, V59_19.1, V59_20.1, V59_21.1, V59_22.1, V59_23.1, V59_24.1, V59_25.1, V59_26.1, V59_27.1, V59_28.1, V59_34.1, V59_35.1, V60_1.1, V60_2.1, V60_4.1, V60_5.1, V60_6.1, V60_8.1, V60_9.1, V60_10.1, V60_11.1, V60_12.1, V60_13.1, V60_14.1, V60_15.1, V60_16.1, V60_17.1, V60_18.1, V60_19.1, V60_20.1, V60_21.1, V60_22.1, V60_23.1, V60_24.1, V60_25.1, V60_26.1, V60_27.1, V60_28.1, V60_34.1, V60_35.1, V61_1.1, V61_32.1, V61_35.1, V62_1.1, V62_2.1, V62_4.1, V62_32.1, V62_34.1, V62_35.1, V63_2.1, V63_3.1, V63_4.1, V63_32.1, V63_33.1, V63_34.1, V63_35.1
ISOGND: C11.1, C19.2, C24.2, C25.2, C29.1, C38.1, J6.4, R4.2, R5.1, R14.2, R15.1, R19.2, R20.1, T2.5, U3.4, U7.2, U9.4, U12.4
unnamed: C10.1, C15.1, D1.1, D2.1, U4.1, U4.3
unnamed: C19.1, C24.1, D3.1, D4.1, U7.1, U7.3
unnamed: D1.2, T1.6
unnamed: D2.2, T1.4
unnamed: D3.2, T2.6
unnamed: D4.2, T2.4
unnamed: J1.5, P1.15
unnamed: J1.6, P1.11
unnamed: J2.5, P2.15
unnamed: J2.6, P2.11
unnamed: J3.5, P3.15
unnamed: J3.6, P3.11
unnamed: R1.1, R3.2
unnamed: R1.2, R21.1
unnamed: R6.1, R8.2
unnamed: R11.1, R13.2
unnamed: R11.2, R23.1
unnamed: R16.1, R18.2
unnamed: R16.2, R24.1
unnamed: R6.2, R22.1
unnamed: T1.1, U2.3
unnamed: T1.3, U2.1
unnamed: T2.1, U5.3
unnamed: T2.3, U5.1
~FAULT_U: J1.12, P1.9, P1.13
~FAULT_V: J2.12, P2.9, P2.13
~FAULT_W: J3.12, P3.9, P3.13

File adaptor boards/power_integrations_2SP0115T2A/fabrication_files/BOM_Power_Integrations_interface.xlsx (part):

|  |  |  |  |  |  | Board Qty: | 10
 |  |  |  |  |  |  | Total Cost: | 1107.350708 |  |  |  | 547.414 |  |  |  |  |  | 442.052802 |  |  |  |  |  | 892.66 |  |  |  |  |  | 507.91 |  |  |  |  |  | 2786.39938
 |  |  |  |  |  |  | Unit Cost: | 110.7350708
Global Part Info |  |  |  |  |  |  |  |  | Digi-Key |  |  |  |  |  | Farnell |  |  |  |  |  | Mouser |  |  |  |  |  | Newark |  |  |  |  |  | Rs Components
Refs | Value | Desc | Footprint | Manf | Manf# | Qty | Unit$ | Ext$ | Avail | Purch | Unit$ | Ext$ | Cat# | Doc | Avail | Purch | Unit$ | Ext$ | Cat# | Doc | Avail | Purch | Unit$ | Ext$ | Cat# | Doc | Avail | Purch | Unit$ | Ext$ | Cat# | Doc | Avail | Purch | Unit$ | Ext$ | Cat# | Doc
P1-P3 | 2SP0115T_conector |  | conn-100mil:CONN-100MIL-F-2x10 | Amphenol FCI | 75869-104LF | 30 | 0.973708 | 29.21124 | 1894 |  | 1.195 | 35.85 | 609-1776-ND | Link |  |  | 0.973708 | 29.21124 | 1103952 | Link | 481 |  | 1.08 | 32.4 | 649-75869-104LF | Link |  |  | 1.01 | 30.3 | 93K5090 | Link | 150 |  | 0.99922 | 29.9766 | 673-7600 | Link
R2,R7,R12,R17 | 20k |  | IPC7351-Nominal:RESC6432X70 |  | CRCW251220K0JNEG | 40 | 0.12756 | 5.1024 | 12547 |  | 0.348 | 13.92 | 541-20KXCT-ND | Link |  |  | 0.173269 | 6.93076 | 1571740 | Link | 1615 |  | 0.216 | 8.64 | 71-CRCW2512J-20K-E3 | Link |  |  | 0.185 | 7.4 | 89M6939 | Link |  |  | 0.12756 | 5.1024 | 842-9496 | Link
U3,U6,U9,U12 | AMC1301 |  | IPC7351-Nominal:SOIC127P1032X265-8 | Texas Instruments | AMC1301DWVR | 40 | 5.651 | 226.04 | 3988 |  | 5.651 | 226.04 | 296-44577-1-ND | Link |  |  | 5.7402 | 229.608 | 2617071 | Link |  |  |  |  |  |  |  |  | 7.03 | 281.2 | 96Y8999 | Link
C11,C20,C29,C38 | 100nF |  | IPC7351-Nominal:CAPC1608X55 | Murata Electronics North America | GRM188R71E104KA01D | 40 | 0.019134 | 0.76536 | 9708975 |  | 0.086 | 3.44 | 490-1524-1-ND | Link |  |  |  |  | 1828899 | Link |  |  |  |  |  |  |  |  |  |  | 14T3317 | Link |  |  | 0.019134 | 0.76536 | 723-5638 | Link
U4,U7 | TPS76350 |  | smd-semi:SOT-23-5 | Texas Instruments | TPS76350DBVR | 20 | 0.763 | 15.26 | 2878 |  | 0.857 | 17.14 | 296-2707-1-ND | Link |  |  | 0.811069 | 16.22138 | 2764732 | Link |  |  |  |  |  |  |  |  | 0.763 | 15.26 | 77C1037 | Link |  |  |  |  | 661-4242 | Link
J3 | GATE_DRIVER_CONN_W |  | conn-100mil:CONN-100MIL-M-2x8 | Amphenol FCI | 87606-308LF | 10 | 1.77 | 17.7 | 1177 |  | 1.965 | 19.65 | 609-3554-ND | Link |  |  | 1.99844 | 19.9844 | 1278235 | Link | 346 |  | 1.77 | 17.7 | 649-87606-308LF | Link |  |  | 1.92 | 19.2 | 63K0748 | Link |  |  | 1.829423 | 18.29423 | 859-9488 | Link
J4 | VBUS |  | w_conn_jst-ph:b4b-ph-kl | JST Sales America Inc. | B4B-PH-K-S(LF)(SN) | 10 | 0.142442 | 1.42442 | 77385 |  | 0.227 | 2.27 | 455-1706-ND | Link |  |  | 0.142442 | 1.42442 | 9492437 | Link |  |  |  |  | Not Assigned | Link |  |  | 0.232 | 2.32 | 37K9958 | Link | 740 |  | 0.165828 | 1.65828 | 820-1434 | Link
J6 | Phoenix 1757268 5.08mm |  | w_conn_screw:mstba_2,5%2f4-g-5,08 | Phoenix Contact | 1757268 | 10 | 0.562327 | 5.62327 |  |  |  |  |  |  |  |  | 0.562327 | 5.62327 | 3705195 | Link | 2637 |  | 1.23 | 12.3 | 651-1757268 | Link |  |  | 1.21 | 12.1 | 71C4163 | Link | 240 |  | 0.75473 | 7.5473 | 189-6127 | Link
D2,D4 | MBR0520 |  | smd-semi:SOD-123 | ON Semiconductor | MBR0520LT1G | 20 | 0.047 | 0.94 |  |  | 0.3 | 6 | MBR0520LT1GOSCT-ND | Link |  |  | 0.1063 | 2.126 | 9556915 | Link |  |  |  |  |  |  |  |  | 0.047 | 0.94 | 94W8549 | Link |  |  | 0.087166 | 1.74332 | 463-432 | Link
D1,D3 | MBR0520 |  | smd-semi:SOD-123 | ON Semiconductor | MBR0520LT1G | 20 | 0.047 | 0.94 |  |  | 0.3 | 6 | MBR0520LT1GOSCT-ND | Link |  |  | 0.1063 | 2.126 | 9556915 | Link |  |  |  |  |  |  |  |  | 0.047 | 0.94 | 94W8549 | Link |  |  | 0.087166 | 1.74332 | 463-432 | Link
C9,C13,C15,C18,C22,C24,C31,C40 | 100nF |  | IPC7351-Nominal:CAPC1608X55 | Murata Electronics North America | GRM188R71E104KA01D | 80 | 0.019134 | 1.53072 | 9708975 |  | 0.086 | 6.88 | 490-1524-1-ND | Link |  |  |  |  | 1828899 | Link | 16365 |  | 0.041 | 3.28 | 81-GRM39X104K25 | Link |  |  |  |  | 14T3317 | Link |  |  | 0.019134 | 1.53072 | 723-5638 | Link
T1,T2 | TRANS-2CT |  | manuf:WURTH-760390014 | Wurth Electronics Midcom | 760390014 | 20 | 1.71 | 34.2 | 22005 |  | 1.71 | 34.2 | 732-4458-1-ND | Link |  |  |  |  |  |  | 12153 |  | 2.02 | 40.4 | 710-760390014 | Link
J8-J10 | current sensor |  | w_conn_jst-ph:b4b-ph-kl | JST Sales America Inc. | B4B-PH-K-S(LF)(SN) | 30 | 0.142442 | 4.27326 | 77385 |  | 0.227 | 6.81 | 455-1706-ND | Link |  |  | 0.142442 | 4.27326 | 9492437 | Link |  |  |  |  | Not Assigned | Link |  |  | 0.201 | 6.03 | 37K9958 | Link | 740 |  | 0.165828 | 4.97484 | 820-1434 | Link
R1,R3,R6,R8,R11,R13,R16,R18,R21-R24 | 500k |  | IPC7351-Nominal:RESC3216X60 | Yageo | AC1206FR-071ML | 120 | 0.018 | 2.16 | 4081 |  | 0.0247 | 2.964 | YAG3832CT-ND | Link |  |  |  |  |  |  | 11380 |  | 0.018 | 2.16 | 603-AC1206FR-071ML | Link |  |  |  |  |  |  | 5 |  | 21.75961 | 2611.1532 | 618-0708 | Link
R4,R5,R9,R10,R14,R15,R19,R20 | 1k |  | IPC7351-Nominal:RESC1608X50 | Yageo | RC0603FR-071KL | 80 | 0.0081851 | 0.654808 | 12991051 |  | 0.015 | 1.2 | 311-1.00KHRCT-ND | Link |  |  | 0.0081851 | 0.654808 | 9238484 | Link | 3078901 |  | 0.009 | 0.72 | 603-RC0603FR-071KL | Link |  |  | 0.01 | 0.8 | 68R0042 | Link
U1 | LM1117IMP-v.v |  | smd-semi:SOT-223 | ON Semiconductor | NCV1117ST50T3G | 10 | 0.651619 | 6.51619 | 3864 |  | 0.782 | 7.82 | NCV1117ST50T3GOSCT-ND | Link |  |  | 1.033236 | 10.33236 | 2534280 | Link | 2810 |  | 0.715 | 7.15 | 863-NCV1117ST50T3G | Link |  |  | 0.821 | 8.21 | 81Y6964 | Link | 240 |  | 0.651619 | 6.51619 | 802-1743 | Link
J5 | CONN-100MIL-F-1x2 |  | w_conn_screw:mstba_2,5%2f2-g-5,08 | Phoenix Contact | 1923869 | 10 | 0.525122 | 5.25122 | 565 |  | 0.685 | 6.85 | 277-6570-ND | Link |  |  | 0.525122 | 5.25122 | 2776387 | Link | 100 |  | 0.687 | 6.87 | 651-1923869 | Link |  |  | 0.673 | 6.73 | 32AC7953 | Link |  |  |  |  | 859-8303 | Link
C8,C14,C17,C23,C32,C41 | 2.2uF |  | IPC7351-Nominal:CAPC1608X55 | Murata Electronics North America | GRM188R71A225KE15D | 60 | 0.12756 | 7.6536 | 1297812 |  | 0.199 | 11.94 | 490-4520-1-ND | Link |  |  | 0.12756 | 7.6536 | 1797012 | Link |  |  | 0.219 | 13.14 | 81-GRM188R71A225KE15 | Link |  |  | 0.148 | 8.88 | 72R4209 | Link | 900 |  | 0.132875 | 7.9725 | 723-5597 | Link
C1,C4,C10,C16,C19,C25 | 22uF |  | IPC7351-Nominal:CAPC2012X70 | TDK Corporation | C2012X5R1V226M125AC | 60 | 0.603784 | 36.22704 | 136916 |  | 0.863 | 51.78 | 445-14428-1-ND | Link |  |  | 0.603784 | 36.22704 | 2528773 | Link |  |  | 1.1 | 66 | 810-C2012X5R1V226MAC | Link |  |  | 0.756 | 45.36 | 78Y9944 | Link |  |  | 0.814258 | 48.85548 | 915-9334 | Link
C2,C3,C5-C7 | 100nF |  | IPC7351-Nominal:CAPC1608X55 | Murata Electronics North America | GRM188R71E104KA01D | 50 | 0.019134 | 0.9567 | 9708975 |  | 0.086 | 4.3 | 490-1524-1-ND | Link |  |  |  |  | 1828899 | Link |  |  |  |  |  |  |  |  |  |  | 14T3317 | Link |  |  | 0.019134 | 0.9567 | 723-5638 | Link
J2 | GATE_DRIVER_CONN_V |  | conn-100mil:CONN-100MIL-M-2x8 | Amphenol FCI | 87606-308LF | 10 | 1.77 | 17.7 | 1177 |  | 1.965 | 19.65 | 609-3554-ND | Link |  |  | 1.99844 | 19.9844 | 1278235 | Link | 346 |  | 1.77 | 17.7 | 649-87606-308LF | Link |  |  | 1.92 | 19.2 | 63K0748 | Link |  |  | 1.829423 | 18.29423 | 859-9488 | Link
C12,C21,C30,C39 | 330pF |  | IPC7351-Nominal:CAPC1608X55 | Murata Electronics North America | GCM1885C1H331JA16D | 40 | 0.025512 | 1.02048 | 63781 |  | 0.094 | 3.76 | 490-4964-1-ND | Link |  |  | 0.0262561 | 1.050244 | 2688476 | Link |  |  |  |  |  |  |  |  | 0.046 | 1.84 | 06AC6012 | Link | 1400 |  | 0.025512 | 1.02048 | 815-1314 | Link
J1 | GATE_DRIVER_CONN_U |  | conn-100mil:CONN-100MIL-M-2x8 | Amphenol FCI | 87606-308LF | 10 | 1.77 | 17.7 | 1177 |  | 1.965 | 19.65 | 609-3554-ND | Link |  |  | 1.99844 | 19.9844 | 1278235 | Link | 346 |  | 1.77 | 17.7 | 649-87606-308LF | Link |  |  | 1.92 | 19.2 | 63K0748 | Link |  |  | 1.829423 | 18.29423 | 859-9488 | Link
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
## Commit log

2017-01-23 First commit. Added .gitignore
2017-01-23 Added libraries and kicad project
2017-01-24 Added base VESC 4.xx schematic, added protection features, signal conditioning and pcb form factor
2017-01-25 Updated MCU sheet to comply with VESC 6 pinout. Added 5v analog inputs and updated some labels
2017-01-26 Components placement, 3D models, updated some footprints to nominal IPC type
2017-01-26 Added terminal blocks and power supplies
2017-01-27 Added lp filters, fuses, tvs and power symbols
2017-01-27 Added bus voltage conditioning, %v to accel and regen inputs, regulator diode, annotated schematic
2017-01-28 Fixed issue with non-bidirectional phase current measurement. Started routing power supplies. Changed terminal blocks from 5.00mm to 3.81mm pitch
2017-01-29 More layout
2017-01-29 More layout. Changed LED pin. Added placeholder for a resolver IC
2017-01-30 Added reverse polarity protection on the isolated side of CON connector. Also, more layout
2017-01-31 Resolver routed using push pull buffer
2017-01-31 Resolver routed. Added 12v regulator. The screw terminals were backwards(!). Started clearing up DRC markers.
2017-02-01 Routing complete. Added 3D models. No DRC errors, a few ERC warnings
2017-02-01 Added frequency set resistors for the resolver. Fixed protection mosfet installed backwards. More 3D models
2017-02-02 Moved references
2017-02-03 Had a missing pullup for the fault signal. Added silkcreens on the bottom
2017-02-05 Silkscreen logos, fixed swapped OCP inputs, added a button to enter bootloader,missing 3d model.
2017-02-06 Added pinout image
2017-02-06 Added some datasheets
2017-02-06 Files sent to the manufacturer. This is VESC-controller v0.1
2017-02-07 Updated component values according to simulations. 1.5khz for user inputs and 240khz lp pass filters for motor control
2017-02-07 Completed some part numbers
2017-02-07 Completed part number, manufacturer, etc fields. Simulated analog conditioning
2017-02-08 Added README.md
2017-02-08 Trying workaround for the readme images
2017-02-13 Added power integrations igbt driver interface board
2017-02-13 Added power integrations igbt driver documents
2017-02-13 Added power integrations 3d assembly project
2017-04-19 Corrected phase current gain. More 3d models
2017-06-16 Fix inverted diff signals
2017-06-17 Added individual temperature sensing for each half bridge and 2 pwm gpio with low side driver
2017-06-22 Higher resolution pinout diagram
2017-06-30 Fixed power supply inductor footprints in the layout
2017-07-06 Updated layout. DRC OK, moved silkscreen, bumped version to 0.2. Added portable 3d models
2017-08-16 Add BOM
2017-10-20 Added RC filter to FAULT line to prevent noise triggering it
2017-10-20 Fix swapped differential signals in the interface board
2017-10-20 Added general documentation of the power integrations interface board
2017-10-20 Not sure if I ran the DRC so lets push again with DRC checked.
2017-10-20 Add fabrication files for controller board
2017-10-20 Added fabrication files for IGBT driver interface from power integrations
2023-09-28 Add missing lib
